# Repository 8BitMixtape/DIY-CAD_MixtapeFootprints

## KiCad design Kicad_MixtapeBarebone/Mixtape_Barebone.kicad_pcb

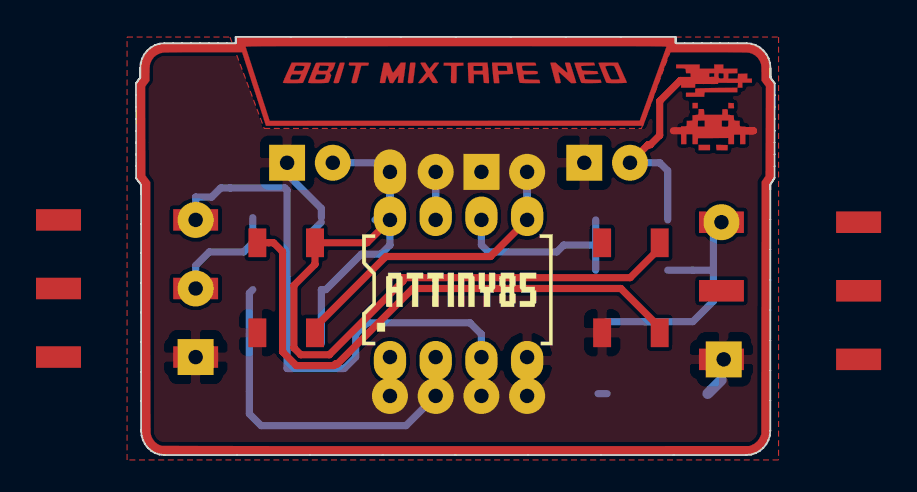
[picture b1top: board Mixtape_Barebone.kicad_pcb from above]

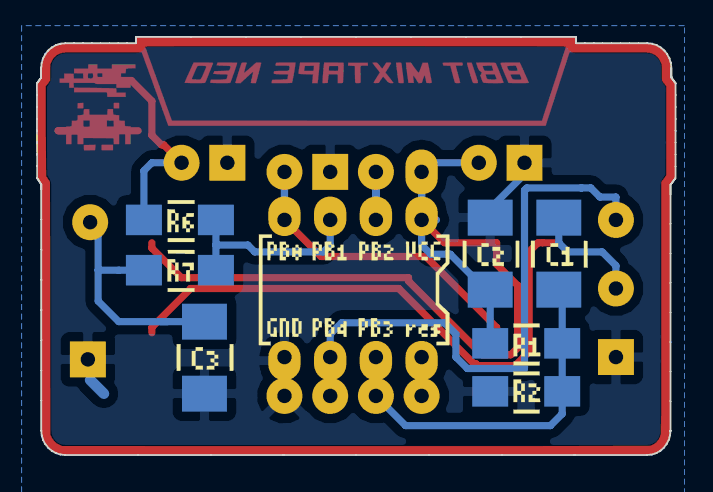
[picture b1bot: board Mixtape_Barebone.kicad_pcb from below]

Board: 2 copper layers, 35.5 x 23.2 mm, 30 parts (7 on the bottom side), 12 nets.

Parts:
C1, C2, C3: 100nF; C_1210_MixtapeStyle
D1: LED; TOP_led_footprint
IC1: ATTINY85-20PU; Attiny_DIP-8_W7.62mm
J1: PB5; Loch_mixtape_seltsam
J2: PB3; Loch_mixtape_seltsam
J3: PB4; Loch_mixtape_seltsam
J3#2: PB4; Loch_mixtape
J4, J4#2: GND; Loch_mixtape_seltsam
J4#3, J4#4, J4#5, J4#6: GND; GND_Loch_mixtape
J5: PB0; Loch_mixtape_seltsam
J7: PB2; Loch_mixtape_seltsam
J8: VCC; Loch_mixtape_seltsam
J8#2: VCC; Loch_mixtape
J9: Prog; Loch_mixtape
J10: S-Out; Loch_mixtape
J11: LED; Loch_mixtape
JACK1, JACK2: JACK_TRS_6PINS; AUDIO-JACK-3.5mm_SMD_noPrint
NEO1, NEO2: SK6813b; Mixtape_NEO_WS2812B
R1, R2: 22K; R_1206_Mixtape
R6: 1K; R_1206_Mixtape
R7: 330; R_1206_Mixtape

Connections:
GND: C2.1, C3.1, D1.1, IC1.4, J4.1, J4#2.1, J4#3.1, J4#4.1, J4#5.1, J4#6.1, JACK1.1, JACK2.1, NEO1.3, NEO2.3, R2.2
NEO: IC1.5, J5.1, NEO1.4
unnamed: C1.2, J9.1, JACK1.3
unnamed: C3.2, J10.1, R7.1
unnamed: D1.2, J11.1, R6.2
unnamed: IC1.1, J1.1
unnamed: IC1.3, J3.1, J3#2.1
unnamed: IC1.6, R6.1, R7.2
unnamed: IC1.7, J7.1
unnamed: NEO1.2, NEO2.4
Prog: C1.1, IC1.2, J2.1, R1.2, R2.1
VCC: C2.2, IC1.8, J8.1, J8#2.1, NEO1.1, NEO2.1, R1.1

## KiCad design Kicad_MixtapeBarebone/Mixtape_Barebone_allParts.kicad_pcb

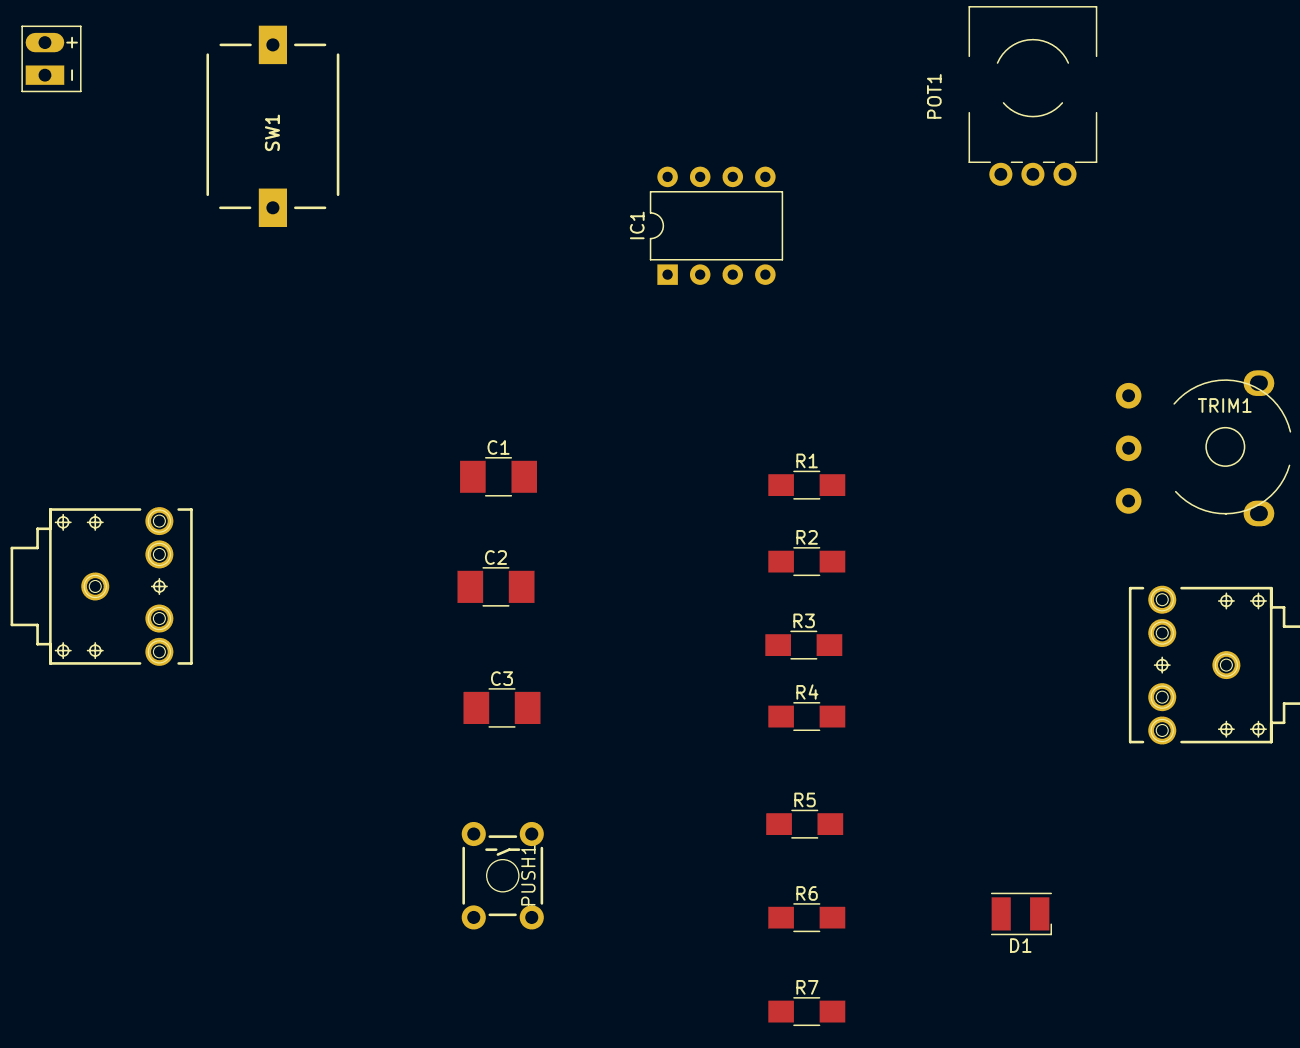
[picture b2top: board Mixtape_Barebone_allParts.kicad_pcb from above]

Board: 2 copper layers, 19 parts (0 on the bottom side), 13 nets, no tracks yet.

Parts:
BAT1: Battery; Bat_connector+-
C1, C2, C3: 100nF; C_1210_MixtapeStyle
D1: LED; LED_2835
IC1: ATTINY85-20PU; DIP-8_W7.62mm
JACK1, JACK2: JACK_TRS_6PINS; AUDIO-Jack_3.5mm_5Pin
POT1: POT; Mixtape_Pot_Alps
PUSH1: SW_Push; TACTILE-PTH_6mm
R1, R2, R3, R4: 22K; R_1206_Mixtape
R5: 4K7; R_1206_Mixtape
R6: 1K; R_1206_Mixtape
R7: 330; R_1206_Mixtape
SW1: SW_SPST; Push_SWITCH-Rect
TRIM1: POT; Potentiometer_wheel

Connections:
+BATT: BAT1.1, SW1.1
GND: BAT1.2, C3.1, D1.1, IC1.4, JACK1.1, JACK2.1, POT1.1, PUSH1.2, R2.2, TRIM1.3
unnamed: C1.1, IC1.3, R1.2, R2.1, R3.1
unnamed: C1.2, JACK1.3
unnamed: C3.2, R7.1, TRIM1.1
unnamed: D1.2, R6.2
unnamed: IC1.6, R6.1, R7.2
unnamed: IC1.7, R4.2
unnamed: JACK2.2, TRIM1.2
unnamed: POT1.2, R4.1
unnamed: POT1.3, R5.1
unnamed: PUSH1.1, R3.2
VCC: C2.2, IC1.8, R1.1, R5.2, SW1.2

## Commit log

2018-07-28 adding stuff
2018-07-28 renaming folders
2018-07-28 MicroBreakout
2018-07-28 Single Sided DIY version
2018-07-29 Designing the MicroCore Barebone Mixtape
2018-08-01 mCore Mixtape and more DIY-CAD stuff
